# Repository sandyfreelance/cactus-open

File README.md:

# cactus-open
Open source documentation, hardware and code for a CubeSat

We provide 4 documents for use by other CubeSat teams, 3 of which comprise our "CubeSat Cookbook".

1) CubeSat_Cookbook_Vol_1_Engineering_Guide.pdf (by R. Pierce Smith) is a comprehensive guide to building your own CubeSat at a detailed engineering level, and includes lessons learned from our Cactus-1 mission.

2) CubeSat_Cookbook_Vol_2_Newcomers_Guide.pdf (by Jorge Rodriguez) is designed for newcomers to CubeSats and discusses some of the overarcing concepts including power, mission readiness reviews, and building effective teams.

3) CubeSat_Cookbook_Vol_3_Common_EPS.pdf (by Erik Schroen) walks you through how to design and customize the electrical power system for your specific CubeSat mission (based on lessons learned from Cactus-1).

4) TheHABHandbook.pdf (by Ian Hastings) is a guide for teams starting up High Altitude Balloon projects.  Under Capitol's "Crawl, Walk, Run" philosophy, we highly recommend teams look at flying payloads and components via HAB as an effective way to iteratively improve your designs.

Acknowledgements: The Cactus-1 mission is Capitol Technology University's first CubeSat mission. Our launch opportunity was provided via the NASA CubeSat Launch Initiative. The Cactus-1 mission is supported by grants from the Maryland Space Grant Consortium (MDSGC).

5) We also provide Ralph Stormer III's "PuzzleSat" 3D-printable CubeSat structure models.  This is a simple modular system for building CubeSat-spec PC104-size-compliant test frames for 1U, 2U, 3U, and other variants so engineering teams can practice working within the CubeSat size requirements.  Documetation, STL and CAD files, and a photo are provided.  They are also fun for prototyping, and we use them for student payload low altitude tests as well.

6) We also provide our hardware schematics, CAD files, and anxillary data to help jumpstart other teams.  Our hardware on this github repository is released under the CERN Open Hardware License version 1.2.  Credit for the Work should be given to R.P. Smith in terms of authorship.  Individual items will indicate citation/credits as well.  Generally, you can use this to build your own CubeSat, the full license terms are below.

* Cactus-1 contains the files for our specific architecture
* CADD Files contains the Cactus-1 stack and board designs used
* EaglePCBs contains PC104, solar, and other bus panels suitable for modding

***********************************************************************

Specific citations and history are given for each component as follows:

Cactus-1 proposals and mission overviews: A. Antunes, R. Schrenk, R. P. Smith, A. Walters, R. Maharaja, M. Horvath

Hermes payload (on Cactus only-- for Hermes sounding rockets, see Maharaja) by C. Murray, E. Schroen (power Board design), Carlos Del Cid, R. Maharaja, P. Smith, IP rights retained by R. Maharaja

Trapsat payload by R. Schrenk, K. Moore, Z. Richards, M. Strittmatter, A. Walters, R. P. Smith, IP rights retained by R. Schrenk

3U++ Tabbed Frame: by R. P. Smith, R. Schrenk, provided under an open hardware license

Pi-CPU/Health & Safety Boards: by R. P. Smith, A. Antunes, provided under an open hardware license

Power bus: by R. P. Smith, G. Auvray, C. Odigwe, A. Antunes, R. Schrenk

Solar: (Added this because power and solar have different aspects (i.e. licensing to use) by R. P. Smith with assembly help from George Gieomekis, Marcus Bailey, Sam Lawson, Nick Keller, Sarah Sharpe, Alex English, Nick Aniello, Chris Finch

Passive Magnetics: by E. Routhier, B Reese , R. P. Smith with help by Ian Hastings, Christina Williams

Flight software by A. Antunes with help by Randy Powell, Zalika Dixon, and thanks to Alan Cudmore for useful discussion on his “PiSat” concept

Thermal blankets by R. Schrenk with help by Sarah Sharpe, Marcus Bailey, and George Giakoumakis

Comms: by M. Horvath, A. Johnson, A. Antunes

Burn wire, foot switches, inhibits, ports, and subsystems not mentioned: considered either part of the above, part of the general Cactus mission, or not sufficiently novel to merit publication or separate enumeration.

Ground team: Mark Horvath, Charis Houston, Devon Marshall, Seth Dickerson

Full list of high-level support (addendum): Alex Antunes, Angela Walters, Rishabh Maharaja, Marcel Mabsen, Patrick Stakem, Alan Cudmore, Dave McComas, Suzanne Strege, Alison Evans, Cinnamon Wright

Full list of students (addendum): Pierce Smith, Ryan Shrenk, Nathan Weideman, Mark Horvath, Alec Johnson, Chris Murray, Sarah Sharpe, George Giakoumakis, Marcus Bailey, Xavier Guzman, Marissa Jagernath, Chukwuma Odigwe, Keegan Moore, Zack Richard, Jamil Ahmed, Gary Visser, Joshua Joseph, Eric Ruthier, Sean Mullin, Christina Williams, Nick Aiello, Randy Powell, Mikus Bormanis, Christel Gesterling, Zalika Dixon, Mike Stritmatter, Josh Hernendez, Ralph Stormer III, Dan Whiteside, Bryce Reese, Charis Houston, Devon Marshall, Seth Dickerson, and others.

uploaded July 2019, updated Dec 2020

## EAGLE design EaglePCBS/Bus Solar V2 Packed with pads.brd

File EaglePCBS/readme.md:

Here are our Cactus-1 solar and bus panels in Eagle CAD format.
Other missions are free to use or repurpose these.readme.md

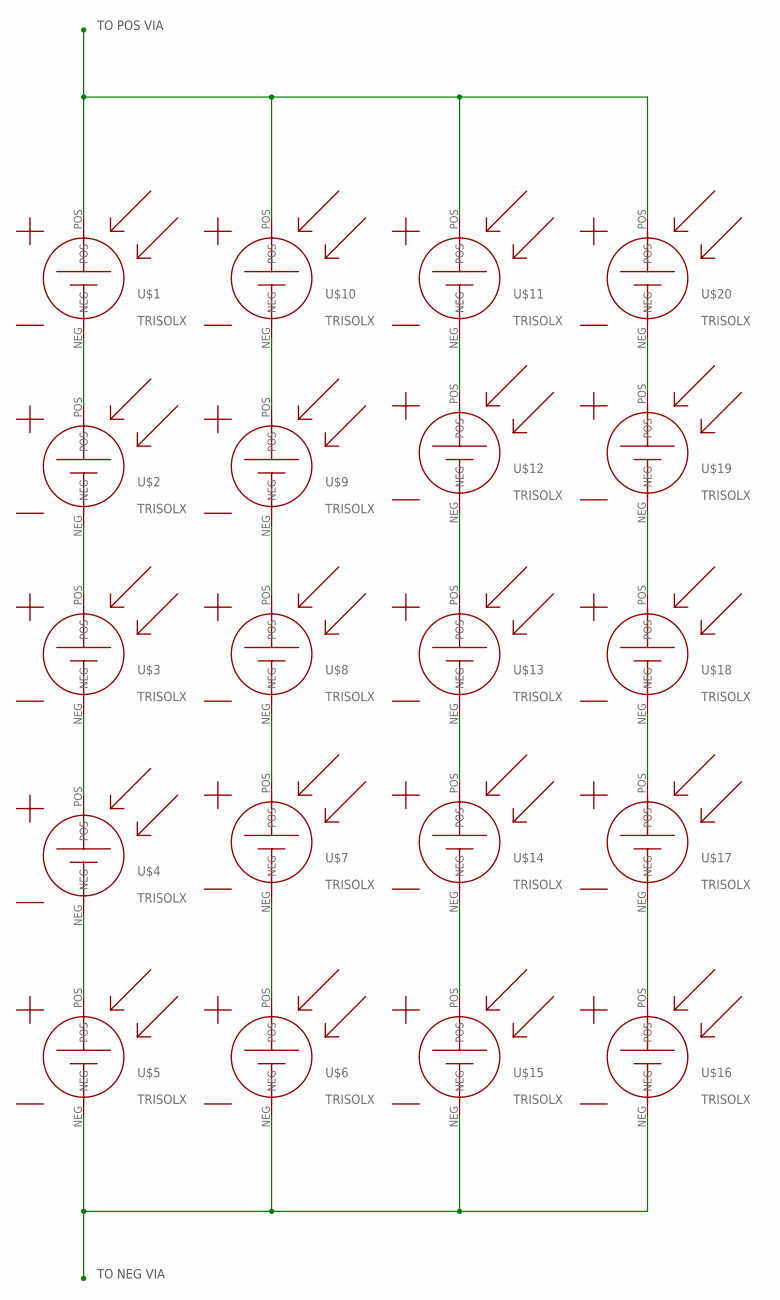
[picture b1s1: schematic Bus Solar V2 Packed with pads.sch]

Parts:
U$1, U$2, U$3, U$4, U$5, U$6, U$7, U$8, U$9, U$10, U$11, U$12, U$13, U$14, U$15, U$16, U$17, U$18, U$19, U$20: TRISOLX

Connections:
unnamed: U$1.NEG, U$2.POS
unnamed: U$2.NEG, U$3.POS
unnamed: U$3.NEG, U$4.POS
unnamed: U$4.NEG, U$5.POS
unnamed: U$9.POS, U$10.NEG
unnamed: U$8.POS, U$9.NEG
unnamed: U$7.POS, U$8.NEG
unnamed: U$6.POS, U$7.NEG
unnamed: U$14.NEG, U$15.POS
unnamed: U$13.NEG, U$14.POS
unnamed: U$12.NEG, U$13.POS
unnamed: U$11.NEG, U$12.POS
unnamed: U$19.POS, U$20.NEG
unnamed: U$18.POS, U$19.NEG
unnamed: U$17.POS, U$18.NEG
unnamed: U$16.POS, U$17.NEG
NEG: U$5.NEG, U$6.NEG, U$15.NEG, U$16.NEG
POS: U$1.POS, U$10.POS, U$11.POS, U$20.POS

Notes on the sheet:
TO POS VIA
TO NEG VIA

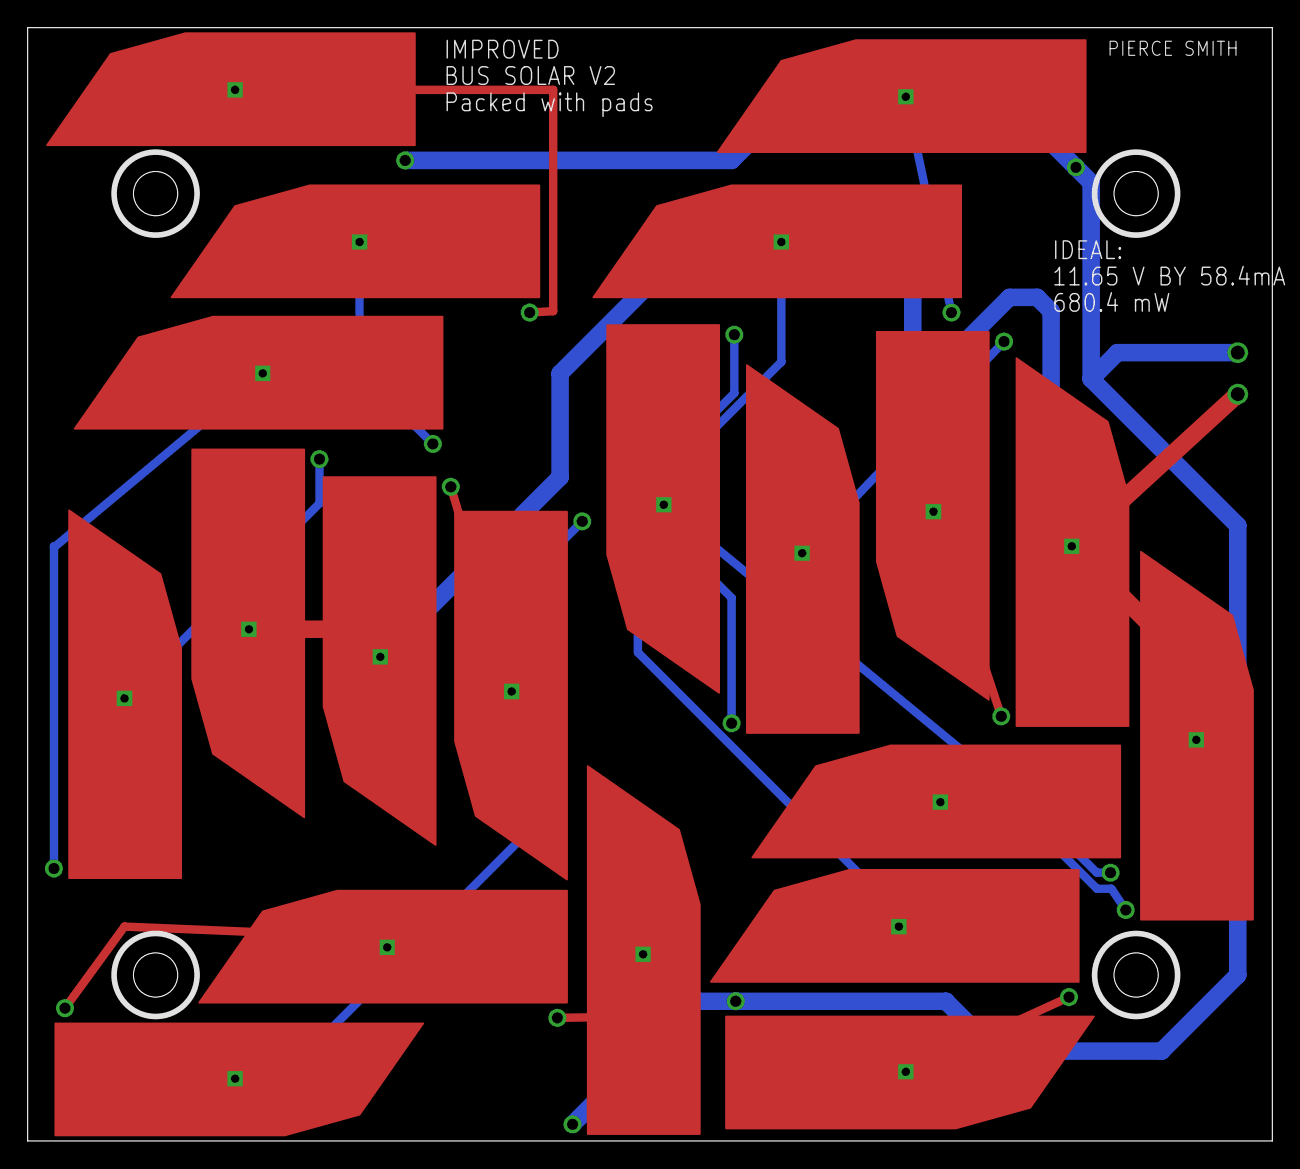
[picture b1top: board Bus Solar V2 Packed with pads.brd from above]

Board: 2 copper layers, 90.0 x 80.5 mm, 20 parts (0 on the bottom side), 18 nets.

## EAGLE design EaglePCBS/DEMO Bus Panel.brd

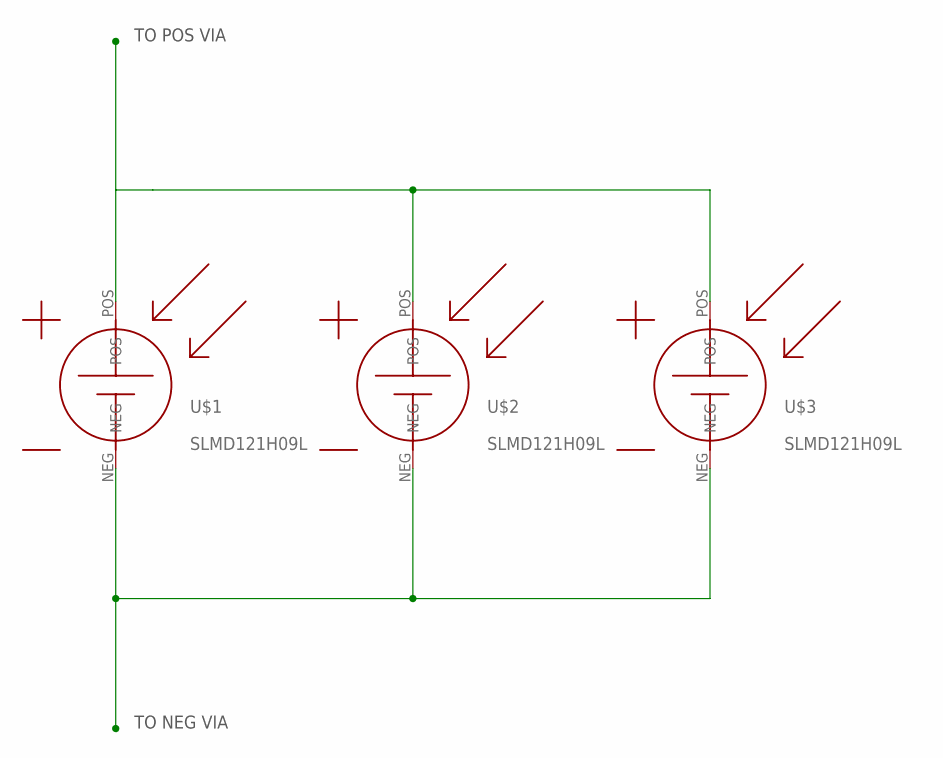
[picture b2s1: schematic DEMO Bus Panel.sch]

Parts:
U$1, U$2, U$3: SLMD121H09L; MONO_SOLAR_CELL_62X21

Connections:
NEG: U$1.NEG, U$2.NEG, U$3.NEG
POS: U$1.POS, U$2.POS, U$3.POS

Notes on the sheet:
TO POS VIA
TO NEG VIA

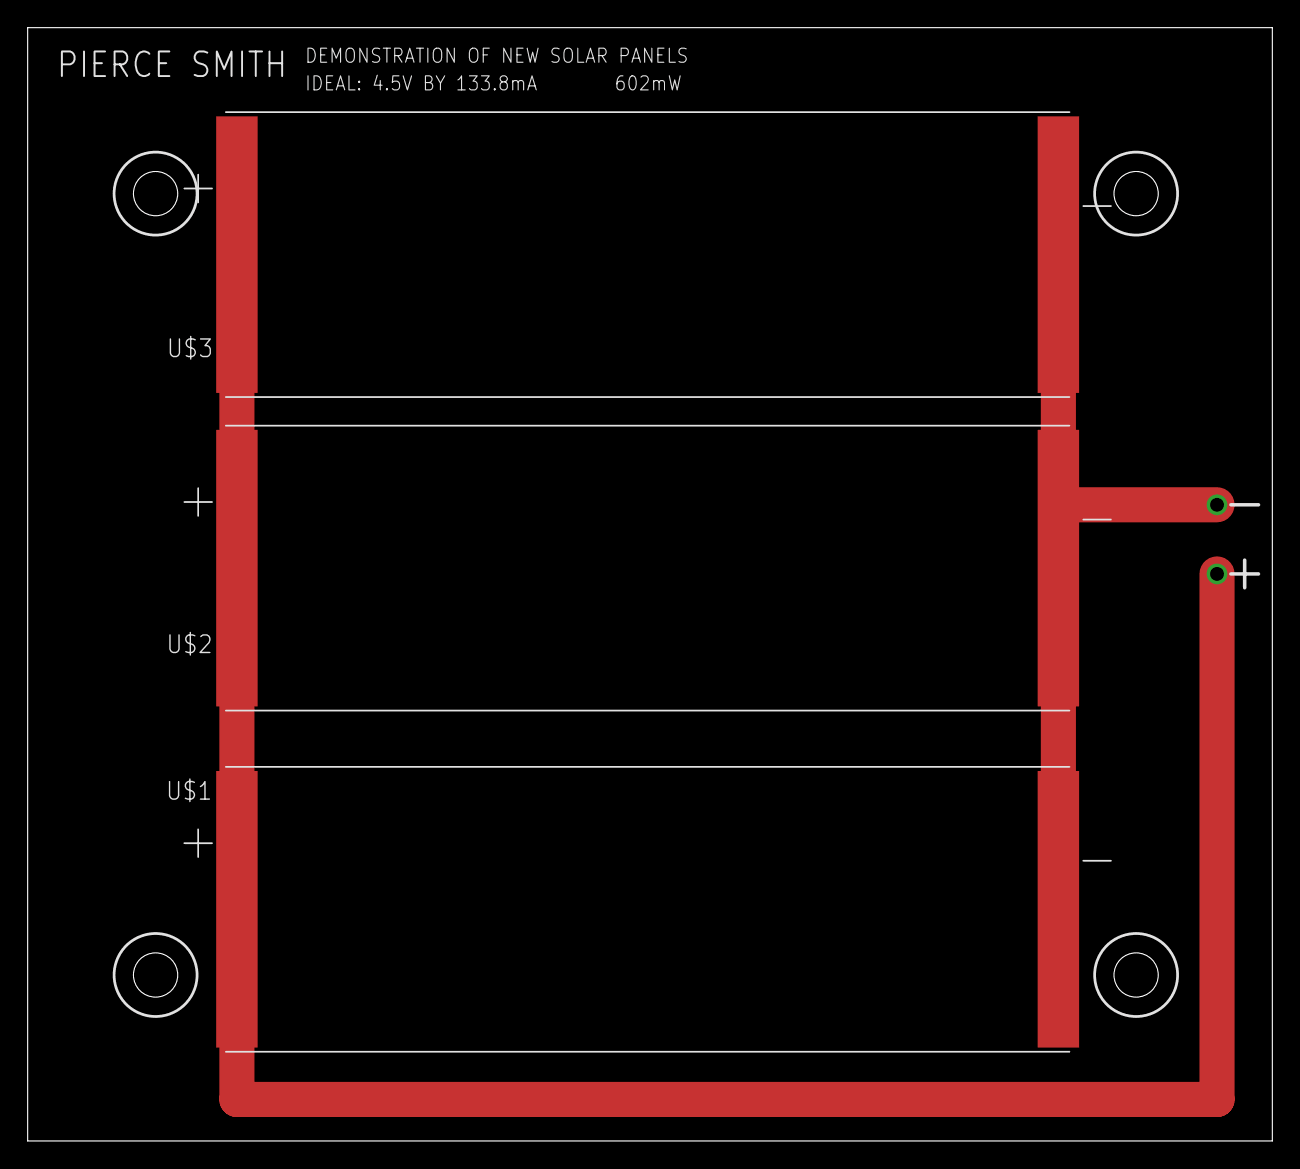
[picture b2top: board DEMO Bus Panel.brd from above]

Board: 2 copper layers, 90.0 x 80.5 mm, 3 parts (0 on the bottom side), 2 nets.

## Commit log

2019-07-30 Delete 3U Payload Vibe Clamp Fixture Rev 1.pdf
    moved to Cactus-1 folder.
2019-07-30 Delete CACTUS - 1 Working drawings Rev1.pdf
    moved to Cactus-1 folder.
2019-07-30 Delete CACTUS-1 PCBs - Sensor, Pi, Solar - Autodesk Eagle.zip
    moved to Cactus-1 folder.
2019-07-30 Delete CACTUS1 Power Board Schematic.pdf
    moved to Cactus-1 folder.
2019-07-30 Delete battery specs NCR18650B.pdf
    moved to Cactus-1 folder.
2019-08-02 added PuzzleSat
